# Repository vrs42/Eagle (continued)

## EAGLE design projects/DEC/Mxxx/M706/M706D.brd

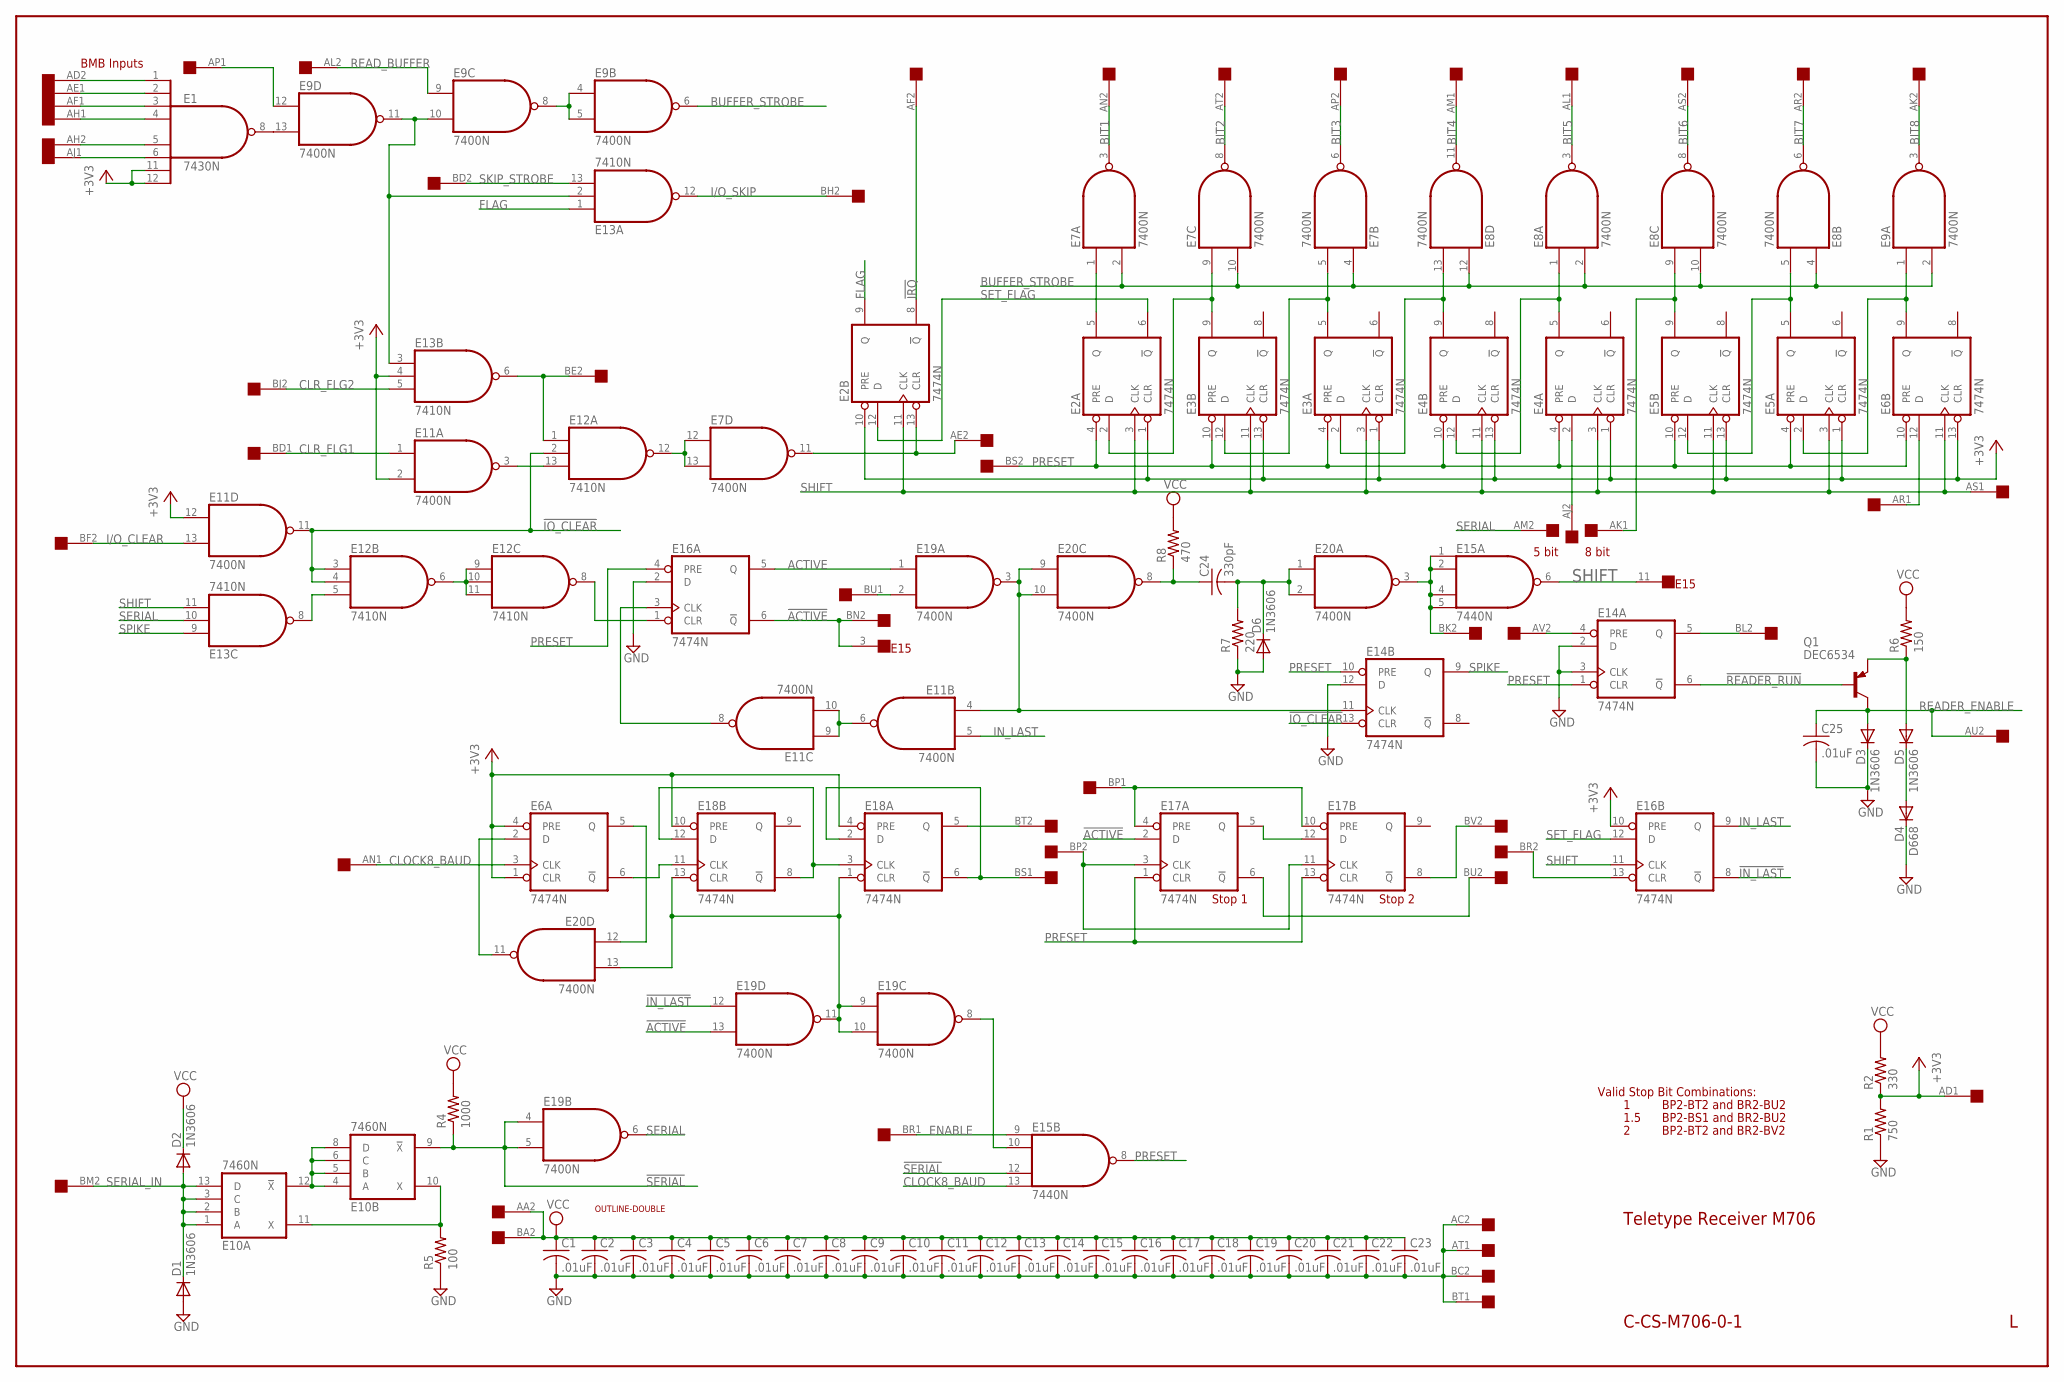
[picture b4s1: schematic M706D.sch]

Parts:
C1, C2, C3, C4, C5, C6, C7, C8, C9, C10, C11, C12, C13, C14, C15, C16, C17, C18, C19, C20, C21, C22, C23, C25: .01uF; C075-032X103
C24: 330pF; C075-032X103
D1, D2, D6: 1N3606; SOD61B
D3, D5: 1N3606; DO35-10
D4: D668; DO35-10
E1: 7430N; DIL14
E2, E3, E4, E5, E6, E14, E16, E17, E18: 7474N; DIL14
E7, E8, E9, E11, E19, E20: 7400N; DIL14
E10: 7460N; DIL14
E12, E13: 7410N; DIL14
E15: 7440N; DIL14
Q1: DEC6534; TO92-EBC
R1: 750; 0207/10
R2: 330; 0207/10
R4: 1000; 0207/15
R5: 100; 0207/15
R6: 150; 0207/10
R7: 220; 0207/15
R8: 470; 0207/15
U$1: OUTLINE-DOUBLE; DOUBLE
U$2: DOUBLE; EDGE-CON4

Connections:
2^0: E6.5 (Q), E20.12 (I0)
!ACTIVE: E15.3 (NC), E16.6 (!Q), E17.2 (D), E19.13 (I1), U$2.BN2
!IN_LAST: E16.8 (!Q), E19.12 (I0)
!IO_CLEAR: E11.11 (O), E12.2 (I1), E12.3 (I0), E12.4 (I1), E14.13 (CLR)
!IRQ: E2.8 (!Q), U$2.AF2
!READER_RUN: E14.6 (!Q), Q1.B
!SERIAL: E10.9 (!X), E15.12 (I2), E19.4 (I0), E19.5 (I1), R4.1
+3V3: E1.11 (I6), E1.12 (I7), E2.1 (CLR), E2.10 (PRE), E3.1 (CLR), E3.13 (CLR), E4.1 (CLR), E4.13 (CLR), E5.1 (CLR), E5.13 (CLR), E6.1 (CLR), E6.4 (PRE), E6.13 (CLR), E11.2 (I1), E11.12 (I0), E13.4 (I1), E16.10 (PRE), E18.4 (PRE), E18.10 (PRE), R1.2, R2.1, U$2.AD1
ACTIVE: E16.5 (Q), E19.1 (I0)
BIT1: E7.3 (O), U$2.AN2
BIT2: E7.8 (O), U$2.AT2
BIT3: E7.6 (O), U$2.AP2
BIT4: E8.11 (O), U$2.AM1
BIT5: E8.3 (O), U$2.AL1
BIT6: E8.8 (O), U$2.AS2
BIT7: E8.6 (O), U$2.AR2
BIT8: E9.3 (O), U$2.AK2
BUFFER_STROBE: E7.2 (I1), E7.4 (I0), E7.10 (I1), E8.2 (I1), E8.4 (I0), E8.10 (I1), E8.12 (I0), E9.2 (I1), E9.6 (O)
CLOCK8_BAUD: E6.3 (CLK), E15.13 (I3), U$2.AN1
CLR_FLG1: E11.1 (I0), U$2.BD1
CLR_FLG2: E13.5 (I2), U$2.BJ2
ENABLE: E15.9 (I0), U$2.BR1
FLAG: E2.9 (Q), E13.1 (I0)
GND: C1.2, C2.2, C3.2, C4.2, C5.2, C6.2, C7.2, C8.2, C9.2, C10.2, C11.2, C12.2, C13.2, C14.2, C15.2, C16.2, C17.2, C18.2, C19.2, C20.2, C21.2, C22.2, C23.2, C25.2, D1.A, D3.C, D4.C, D6.A, E1.7 (GND), E2.7 (GND), E3.7 (GND), E4.7 (GND), E5.7 (GND), E6.7 (GND), E7.7 (GND), E8.7 (GND), E9.7 (GND), E10.7 (GND), E11.7 (GND), E12.7 (GND), E13.7 (GND), E14.2 (D), E14.3 (CLK), E14.7 (GND), E14.12 (D), E15.7 (GND), E16.2 (D), E16.7 (GND), E17.7 (GND), E18.7 (GND), E19.7 (GND), E20.7 (GND), R1.1, R5.1, R7.1, U$2.AC2, U$2.AT1, U$2.BC2, U$2.BT1
I/O_CLEAR: E11.13 (I1), U$2.BF2
I/O_SKIP: E13.12 (O), U$2.BH2
IN_LAST: E11.5 (I1), E16.9 (Q)
unnamed: E15.10 (I1), E19.8 (O)
unnamed: E5.5 (Q), E5.12 (D), E8.5 (I1)
unnamed: E5.2 (D), E6.9 (Q), E9.1 (I0)
unnamed: E5.9 (Q), E8.9 (I0), U$2.AK1
unnamed: E3.5 (Q), E3.12 (D), E7.5 (I1)
unnamed: E3.2 (D), E4.9 (Q), E8.13 (I1)
unnamed: E4.5 (Q), E4.12 (D), E8.1 (I0)
unnamed: E2.5 (Q), E7.1 (I0)
unnamed: E2.2 (D), E3.9 (Q), E7.9 (I0)
unnamed: E1.8 (O), E9.13 (I1)
unnamed: E2.13 (CLR), E7.11 (O), U$2.AE2
unnamed: E7.12 (I0), E7.13 (I1), E12.12 (O)
unnamed: E11.8 (O), E16.3 (CLK)
unnamed: E6.12 (D), U$2.AR1
unnamed: E1.6 (I5), U$2.AJ1
unnamed: E9.12 (I0), U$2.AP1
unnamed: E1.1 (I0), U$2.AD2
unnamed: E1.2 (I1), U$2.AE1
unnamed: E1.3 (I2), U$2.AF1
unnamed: E1.4 (I3), U$2.AH1
unnamed: E1.5 (I4), U$2.AH2
unnamed: E9.4 (I0), E9.5 (I1), E9.8 (O)
unnamed: E9.10 (I1), E9.11 (O), E13.2 (I1), E13.3 (I0)
unnamed: E11.3 (O), E12.13 (I2)
unnamed: E12.1 (I0), E13.6 (O), U$2.BE2
unnamed: E15.1 (I0), E15.2 (I1), E15.4 (I2), E15.5 (I3), E20.3 (O), U$2.BK2
unnamed: E6.2 (D), E20.11 (O)
unnamed: E12.5 (I2), E13.8 (O)
unnamed: E12.6 (O), E12.9 (I0), E12.10 (I1), E12.11 (I2)
unnamed: E4.2 (D), U$2.AJ2
unnamed: E12.8 (O), E16.1 (CLR)
unnamed: E6.6 (!Q), E18.11 (CLK)
unnamed: E18.3 (CLK), E18.8 (!Q), E18.12 (D)
unnamed: E18.5 (Q), U$2.BT2
unnamed: E18.2 (D), E18.6 (!Q), U$2.BS1
unnamed: E17.3 (CLK), E17.11 (CLK), U$2.BP2
unnamed: E10.4 (A), E10.5 (B), E10.6 (C), E10.8 (D), E10.12 (!X)
unnamed: E10.10 (X), E10.11 (X), R5.2
unnamed: E11.6 (O), E11.9 (I0), E11.10 (I1)
unnamed: E11.4 (I0), E14.11 (CLK), E19.3 (O), E20.9 (I0), E20.10 (I1)
unnamed: E18.1 (CLR), E18.13 (CLR), E19.9 (I0), E19.10 (I1), E19.11 (O), E20.13 (I1)
unnamed: C24.1, E20.8 (O), R8.1
unnamed: E14.4 (PRE), U$2.AV2
unnamed: E14.5 (Q), U$2.BL2
unnamed: C24.2, D6.C, E20.1 (I0), E20.2 (I1), R7.2
unnamed: D5.A, Q1.E, R6.1
unnamed: D4.A, D5.C
unnamed: E16.13 (CLR), U$2.BR2
unnamed: E17.6 (!Q), U$2.BU2
unnamed: E17.8 (!Q), U$2.BV2
unnamed: E17.5 (Q), E17.12 (D)
unnamed: E17.4 (PRE), E17.10 (PRE), U$2.BP1
unnamed: E19.2 (I1), U$2.BU1
PRESET: E2.4 (PRE), E3.4 (PRE), E3.10 (PRE), E4.4 (PRE), E4.10 (PRE), E5.4 (PRE), E5.10 (PRE), E6.10 (PRE), E14.1 (CLR), E14.10 (PRE), E15.8 (O), E16.4 (PRE), E17.1 (CLR), E17.13 (CLR), U$2.BS2
READER_ENABLE: C25.1, D3.A, Q1.C, U$2.AU2
READ_BUFFER: E9.9 (I0), U$2.AL2
SERIAL: E13.10 (I1), E19.6 (O), U$2.AM2
SERIAL_IN: D1.C, D2.A, E10.1 (A), E10.2 (B), E10.3 (C), E10.13 (D), U$2.BM2
SET_FLAG: E2.6 (!Q), E2.12 (D), E16.12 (D)
SHIFT: E2.3 (CLK), E2.11 (CLK), E3.3 (CLK), E3.11 (CLK), E4.3 (CLK), E4.11 (CLK), E5.3 (CLK), E5.11 (CLK), E6.11 (CLK), E13.11 (I2), E15.6 (O), E15.11 (NC), E16.11 (CLK), U$2.AS1
SKIP_STROBE: E13.13 (I2), U$2.BD2
SPIKE: E13.9 (I0), E14.9 (Q)
VCC: C1.1, C2.1, C3.1, C4.1, C5.1, C6.1, C7.1, C8.1, C9.1, C10.1, C11.1, C12.1, C13.1, C14.1, C15.1, C16.1, C17.1, C18.1, C19.1, C20.1, C21.1, C22.1, C23.1, D2.C, E1.14 (VCC), E2.14 (VCC), E3.14 (VCC), E4.14 (VCC), E5.14 (VCC), E6.14 (VCC), E7.14 (VCC), E8.14 (VCC), E9.14 (VCC), E10.14 (VCC), E11.14 (VCC), E12.14 (VCC), E13.14 (VCC), E14.14 (VCC), E15.14 (VCC), E16.14 (VCC), E17.14 (VCC), E18.14 (VCC), E19.14 (VCC), E20.14 (VCC), R2.2, R4.2, R6.2, R8.2, U$2.AA2, U$2.BA2

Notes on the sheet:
BMB Inputs
8 bit
5 bit
Stop 1
Stop 2
Valid Stop Bit Combinations:
1.5
BP2-BT2 and BR2-BU2
BP2-BS1 and BR2-BU2
BP2-BT2 and BR2-BV2
Teletype Receiver M706
C-CS-M706-0-1

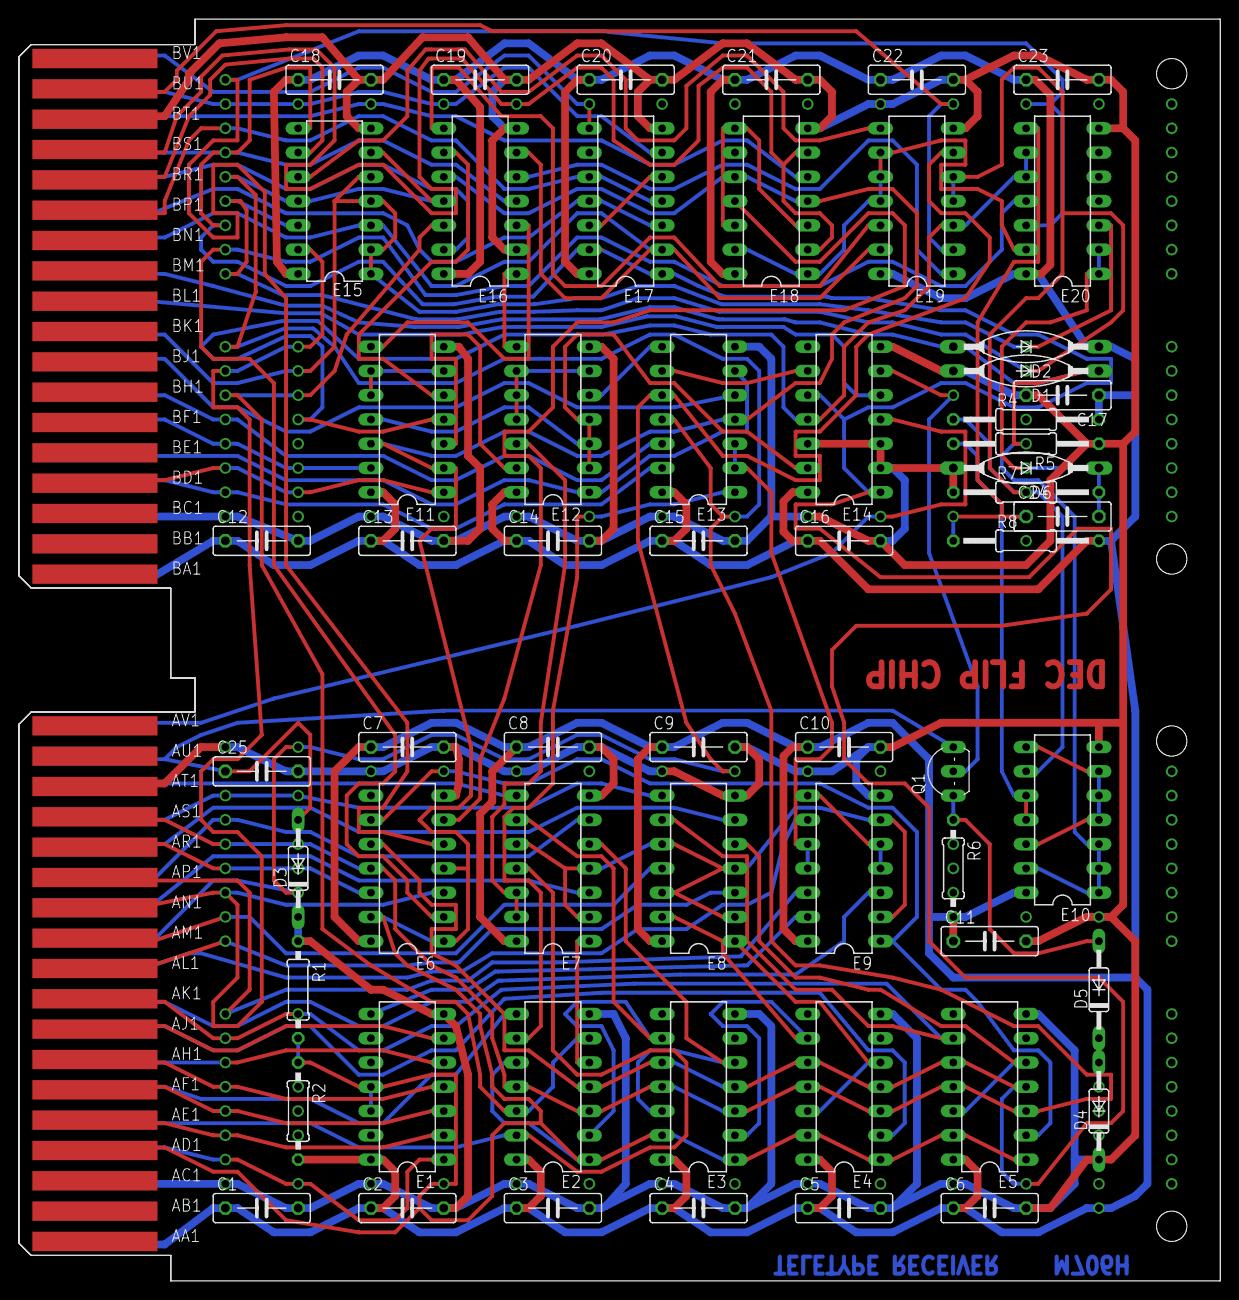
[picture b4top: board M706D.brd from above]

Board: 2 copper layers, 125.7 x 132.1 mm, 61 parts (0 on the bottom side), 90 nets.
